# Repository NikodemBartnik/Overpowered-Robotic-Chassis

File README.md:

# Overpowered Robotic Chassis

This is a repository with examples on how to use T-Motor AK series actuator with Arduino and some python scripts. You can also find 3D models of a simple modular chassis that I used to build a robotic platform for future experiments.
For more info check out this video:\

Useful links:\
https://store.tmotor.com/category.php?id=97
https://docs.google.com/document/d/1dzNVzblz6mqB3eZVEMyi2MtSngALHdgpTaDJIW_BpS4
https://github.com/MihaiMoldovanu/robotic/blob/main/arduino/CAN_bus_robot.ino
https://github.com/dfki-ric-underactuated-lab/mini-cheetah-tmotor-python-can

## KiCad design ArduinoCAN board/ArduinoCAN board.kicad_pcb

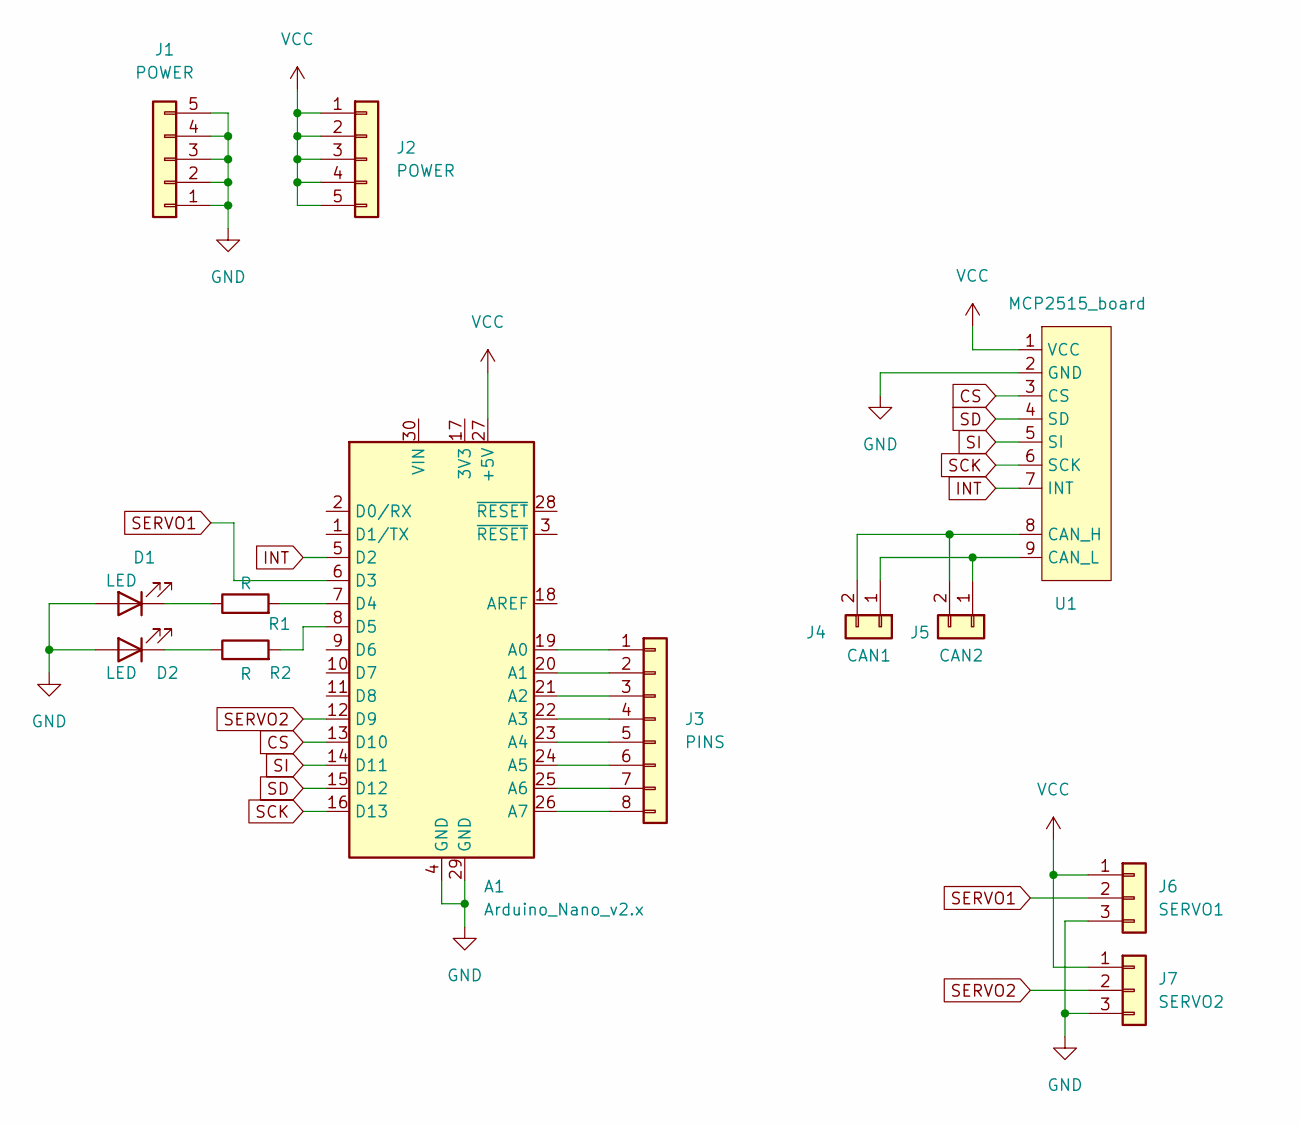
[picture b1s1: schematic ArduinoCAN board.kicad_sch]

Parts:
A1: Arduino_Nano_v2.x; Arduino_Nano
D1, D2: LED; LED_D5.0mm
J1, J2: POWER; PinHeader_1x05_P2.54mm_Vertical
J3: PINS; PinHeader_1x08_P2.54mm_Vertical
J4: CAN1; PinHeader_1x02_P2.54mm_Vertical
J5: CAN2; PinHeader_1x02_P2.54mm_Vertical
J6: SERVO1; PinHeader_1x03_P2.54mm_Vertical
J7: SERVO2; PinHeader_1x03_P2.54mm_Vertical
R1, R2: R; R_1206_3216Metric_Pad1.30x1.75mm_HandSolder
U1: MCP2515_board

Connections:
CS: A1.13 (D10), U1.3 (CS)
GND: A1.4 (GND), A1.29 (GND), D1.2 (A), D2.2 (A), J1.1, J1.2, J1.3, J1.4, J1.5, J6.3, J7.3, U1.2 (GND)
INT: A1.5 (D2), U1.7 (INT)
unnamed: A1.7 (D4), R1.2
unnamed: A1.8 (D5), R2.2
unnamed: A1.19 (A0), J3.1
unnamed: A1.20 (A1), J3.2
unnamed: A1.21 (A2), J3.3
unnamed: A1.22 (A3), J3.4
unnamed: A1.23 (A4), J3.5
unnamed: A1.24 (A5), J3.6
unnamed: A1.25 (A6), J3.7
unnamed: A1.26 (A7), J3.8
unnamed: D1.1 (K), R1.1
unnamed: D2.1 (K), R2.1
unnamed: J4.1, J5.1, U1.9 (CAN_L)
unnamed: J4.2, J5.2, U1.8 (CAN_H)
SCK: A1.16 (D13), U1.6 (SCK)
SD: A1.15 (D12), U1.4 (SD)
SERVO1: A1.6 (D3), J6.2
SERVO2: A1.12 (D9), J7.2
SI: A1.14 (D11), U1.5 (SI)
VCC: A1.27 (+5V), J2.1, J2.2, J2.3, J2.4, J2.5, J6.1, J7.1, U1.1 (VCC)

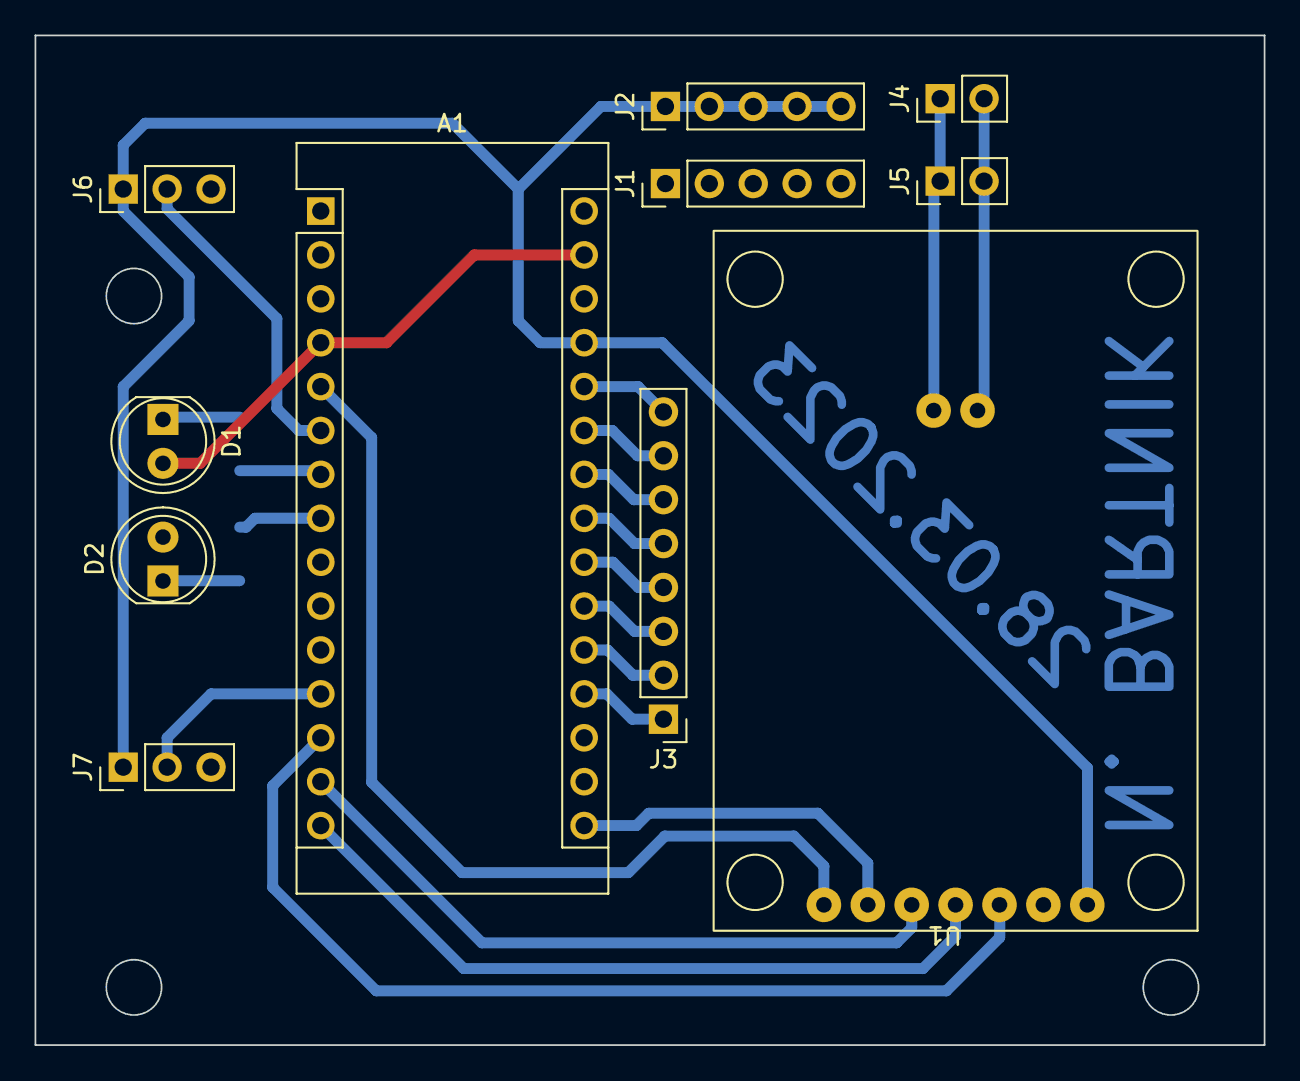
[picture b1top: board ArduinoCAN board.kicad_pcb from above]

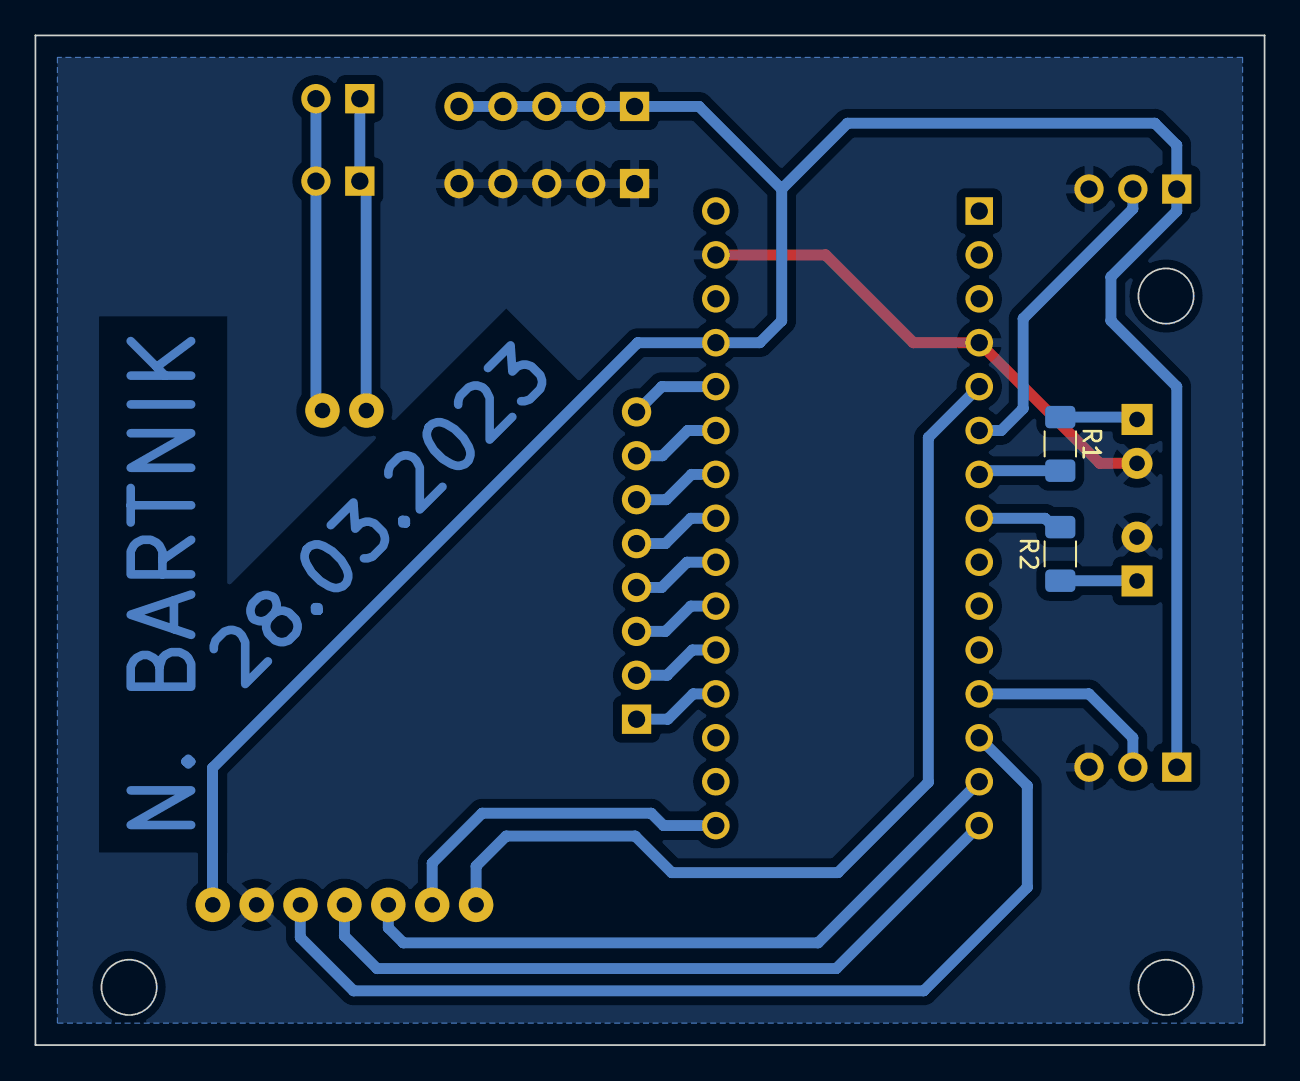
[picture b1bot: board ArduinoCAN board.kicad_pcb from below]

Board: 2 copper layers, 71.1 x 58.4 mm, 13 parts (2 on the bottom side), 23 nets.

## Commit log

2021-12-21 Readme fix
2021-12-21 yet another readme fix
2022-06-24 fixes small typos in README.md
2023-03-24 clean up
2023-03-24 motor controller design started
2023-03-28 PCB finished name change
2023-03-29 updated holders
2023-03-29 added servo, pins and power connectors
2023-03-29 added gerber files
2023-03-29 added gcode files
2023-03-29 added flatcam project
2023-03-29 fixed max Z height in gcode files
2023-04-11 ArduinoCAN board firmware added
2023-04-11 naming changed
2023-05-02 floating speed fix
